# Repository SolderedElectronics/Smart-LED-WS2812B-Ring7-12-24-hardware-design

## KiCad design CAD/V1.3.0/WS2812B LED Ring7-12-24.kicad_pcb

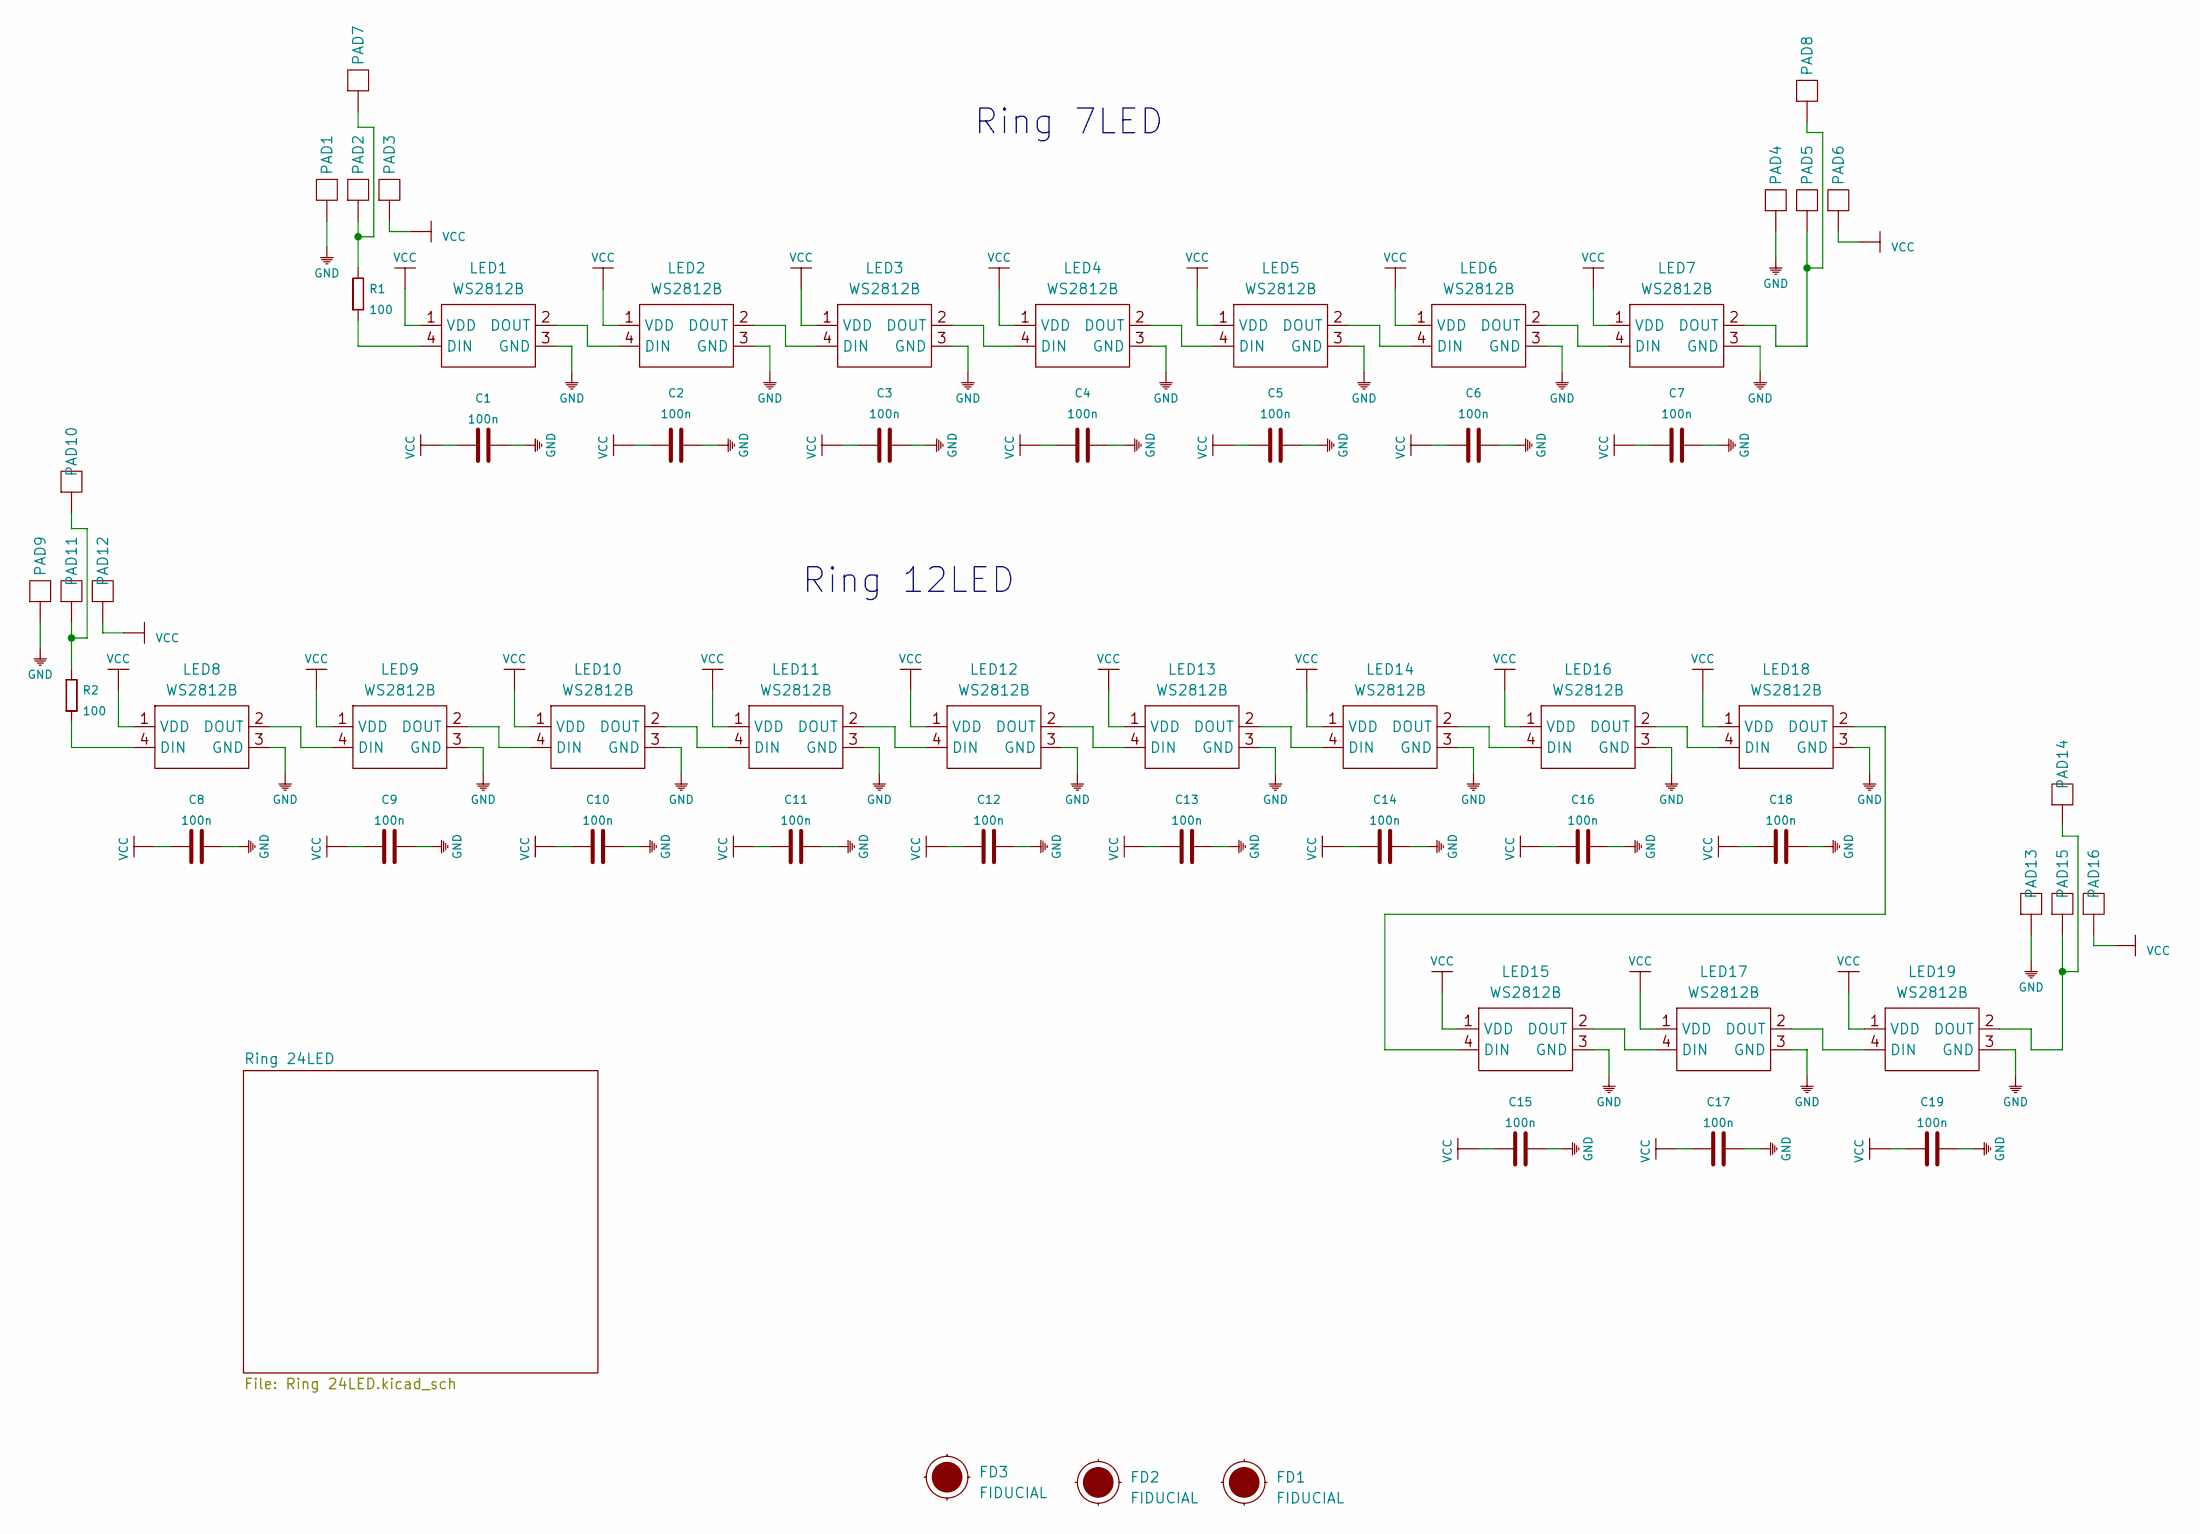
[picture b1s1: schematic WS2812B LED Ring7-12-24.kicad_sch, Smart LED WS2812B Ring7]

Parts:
C1, C2, C3, C4, C5, C6, C7, C8, C9, C10, C11, C12, C13, C14, C15, C16, C17, C18, C19: 100n; 0603C
FD1, FD2, FD3: FIDUCIAL; FIDUCIAL_23
LED1, LED2, LED3, LED4, LED5, LED6, LED7, LED8, LED9, LED10, LED11, LED12, LED13, LED14, LED15, LED16, LED17, LED18, LED19: WS2812B; WS2812B LED
PAD1, PAD2, PAD3, PAD4, PAD5, PAD6, PAD7, PAD8, PAD9, PAD10, PAD11, PAD12, PAD13, PAD14, PAD15, PAD16: PAD_2x1.5
R1, R2: 100; 0603R

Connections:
GND: C1.2, C2.2, C3.2, C4.2, C5.2, C6.2, C7.2, C8.2, C9.2, C10.2, C11.2, C12.2, C13.2, C14.2, C15.2, C16.2, C17.2, C18.2, C19.2, LED1.3 (GND), LED2.3 (GND), LED3.3 (GND), LED4.3 (GND), LED5.3 (GND), LED6.3 (GND), LED7.3 (GND), LED8.3 (GND), LED9.3 (GND), LED10.3 (GND), LED11.3 (GND), LED12.3 (GND), LED13.3 (GND), LED14.3 (GND), LED15.3 (GND), LED16.3 (GND), LED17.3 (GND), LED18.3 (GND), LED19.3 (GND), PAD1.1, PAD4.1, PAD9.1, PAD13.1; also elsewhere on the board
unnamed: LED1.2 (DOUT), LED2.4 (DIN)
unnamed: LED1.4 (DIN), R1.1
unnamed: LED2.2 (DOUT), LED3.4 (DIN)
unnamed: LED3.2 (DOUT), LED4.4 (DIN)
unnamed: LED4.2 (DOUT), LED5.4 (DIN)
unnamed: LED5.2 (DOUT), LED6.4 (DIN)
unnamed: LED6.2 (DOUT), LED7.4 (DIN)
unnamed: LED7.2 (DOUT), PAD5.1, PAD8.1
unnamed: LED8.2 (DOUT), LED9.4 (DIN)
unnamed: LED8.4 (DIN), R2.1
unnamed: LED10.2 (DOUT), LED11.4 (DIN)
unnamed: LED9.2 (DOUT), LED10.4 (DIN)
unnamed: LED11.2 (DOUT), LED12.4 (DIN)
unnamed: LED12.2 (DOUT), LED13.4 (DIN)
unnamed: LED13.2 (DOUT), LED14.4 (DIN)
unnamed: LED14.2 (DOUT), LED16.4 (DIN)
unnamed: LED15.2 (DOUT), LED17.4 (DIN)
unnamed: LED15.4 (DIN), LED18.2 (DOUT)
unnamed: LED16.2 (DOUT), LED18.4 (DIN)
unnamed: LED17.2 (DOUT), LED19.4 (DIN)
unnamed: LED19.2 (DOUT), PAD14.1, PAD15.1
unnamed: PAD2.1, PAD7.1, R1.2
unnamed: PAD10.1, PAD11.1, R2.2
VCC: C1.1, C2.1, C3.1, C4.1, C5.1, C6.1, C7.1, C8.1, C9.1, C10.1, C11.1, C12.1, C13.1, C14.1, C15.1, C16.1, C17.1, C18.1, C19.1, LED1.1 (VDD), LED2.1 (VDD), LED3.1 (VDD), LED4.1 (VDD), LED5.1 (VDD), LED6.1 (VDD), LED7.1 (VDD), LED8.1 (VDD), LED9.1 (VDD), LED10.1 (VDD), LED11.1 (VDD), LED12.1 (VDD), LED13.1 (VDD), LED14.1 (VDD), LED15.1 (VDD), LED16.1 (VDD), LED17.1 (VDD), LED18.1 (VDD), LED19.1 (VDD), PAD3.1, PAD6.1, PAD12.1, PAD16.1; also elsewhere on the board

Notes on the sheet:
Ring 12LED
Ring 7LED

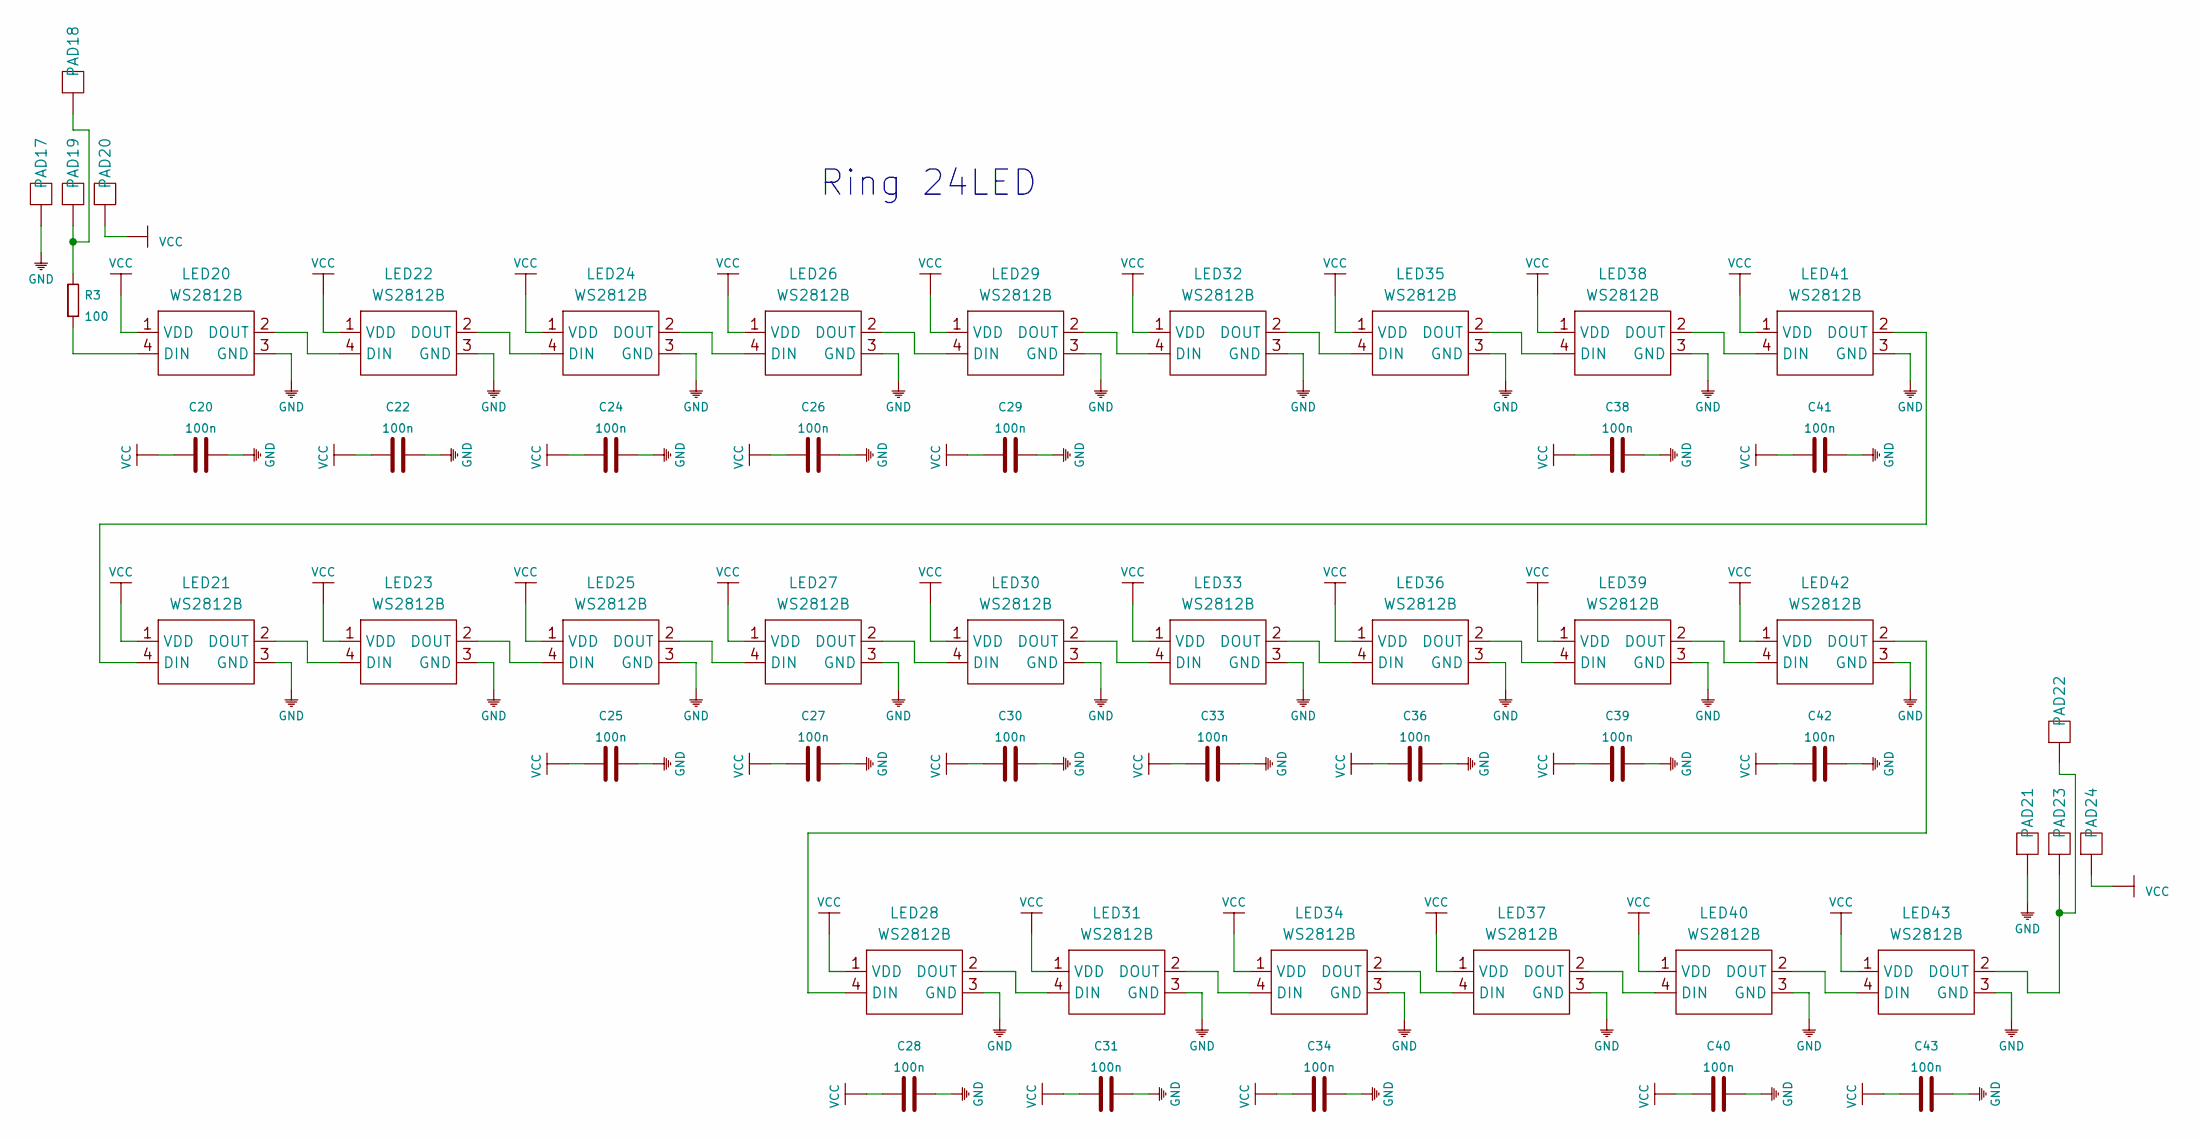
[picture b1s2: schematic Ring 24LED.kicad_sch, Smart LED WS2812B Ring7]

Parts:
C20, C22, C24, C25, C26, C27, C28, C29, C30, C31, C33, C34, C36, C38, C39, C40, C41, C42, C43: 100n; 0603C
LED20, LED21, LED22, LED23, LED24, LED25, LED26, LED27, LED28, LED29, LED30, LED31, LED32, LED33, LED34, LED35, LED36, LED37, LED38, LED39, LED40, LED41, LED42, LED43: WS2812B; WS2812B LED
PAD17, PAD18, PAD19, PAD20, PAD21, PAD22, PAD23, PAD24: PAD_2x1.5
R3: 100; 0603R

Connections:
GND: C20.2, C22.2, C24.2, C25.2, C26.2, C27.2, C28.2, C29.2, C30.2, C31.2, C33.2, C34.2, C36.2, C38.2, C39.2, C40.2, C41.2, C42.2, C43.2, LED20.3 (GND), LED21.3 (GND), LED22.3 (GND), LED23.3 (GND), LED24.3 (GND), LED25.3 (GND), LED26.3 (GND), LED27.3 (GND), LED28.3 (GND), LED29.3 (GND), LED30.3 (GND), LED31.3 (GND), LED32.3 (GND), LED33.3 (GND), LED34.3 (GND), LED35.3 (GND), LED36.3 (GND), LED37.3 (GND), LED38.3 (GND), LED39.3 (GND), LED40.3 (GND), LED41.3 (GND), LED42.3 (GND), LED43.3 (GND), PAD17.1, PAD21.1; also elsewhere on the board
unnamed: LED20.2 (DOUT), LED22.4 (DIN)
unnamed: LED20.4 (DIN), R3.1
unnamed: LED21.2 (DOUT), LED23.4 (DIN)
unnamed: LED21.4 (DIN), LED41.2 (DOUT)
unnamed: LED22.2 (DOUT), LED24.4 (DIN)
unnamed: LED23.2 (DOUT), LED25.4 (DIN)
unnamed: LED24.2 (DOUT), LED26.4 (DIN)
unnamed: LED25.2 (DOUT), LED27.4 (DIN)
unnamed: LED26.2 (DOUT), LED29.4 (DIN)
unnamed: LED27.2 (DOUT), LED30.4 (DIN)
unnamed: LED28.2 (DOUT), LED31.4 (DIN)
unnamed: LED28.4 (DIN), LED42.2 (DOUT)
unnamed: LED29.2 (DOUT), LED32.4 (DIN)
unnamed: LED30.2 (DOUT), LED33.4 (DIN)
unnamed: LED31.2 (DOUT), LED34.4 (DIN)
unnamed: LED32.2 (DOUT), LED35.4 (DIN)
unnamed: LED33.2 (DOUT), LED36.4 (DIN)
unnamed: LED34.2 (DOUT), LED37.4 (DIN)
unnamed: LED35.2 (DOUT), LED38.4 (DIN)
unnamed: LED36.2 (DOUT), LED39.4 (DIN)
unnamed: LED37.2 (DOUT), LED40.4 (DIN)
unnamed: LED38.2 (DOUT), LED41.4 (DIN)
unnamed: LED39.2 (DOUT), LED42.4 (DIN)
unnamed: LED40.2 (DOUT), LED43.4 (DIN)
unnamed: LED43.2 (DOUT), PAD22.1, PAD23.1
unnamed: PAD18.1, PAD19.1, R3.2
VCC: C20.1, C22.1, C24.1, C25.1, C26.1, C27.1, C28.1, C29.1, C30.1, C31.1, C33.1, C34.1, C36.1, C38.1, C39.1, C40.1, C41.1, C42.1, C43.1, LED20.1 (VDD), LED21.1 (VDD), LED22.1 (VDD), LED23.1 (VDD), LED24.1 (VDD), LED25.1 (VDD), LED26.1 (VDD), LED27.1 (VDD), LED28.1 (VDD), LED29.1 (VDD), LED30.1 (VDD), LED31.1 (VDD), LED32.1 (VDD), LED33.1 (VDD), LED34.1 (VDD), LED35.1 (VDD), LED36.1 (VDD), LED37.1 (VDD), LED38.1 (VDD), LED39.1 (VDD), LED40.1 (VDD), LED41.1 (VDD), LED42.1 (VDD), LED43.1 (VDD), PAD20.1, PAD24.1; also elsewhere on the board

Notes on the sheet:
Ring 24LED

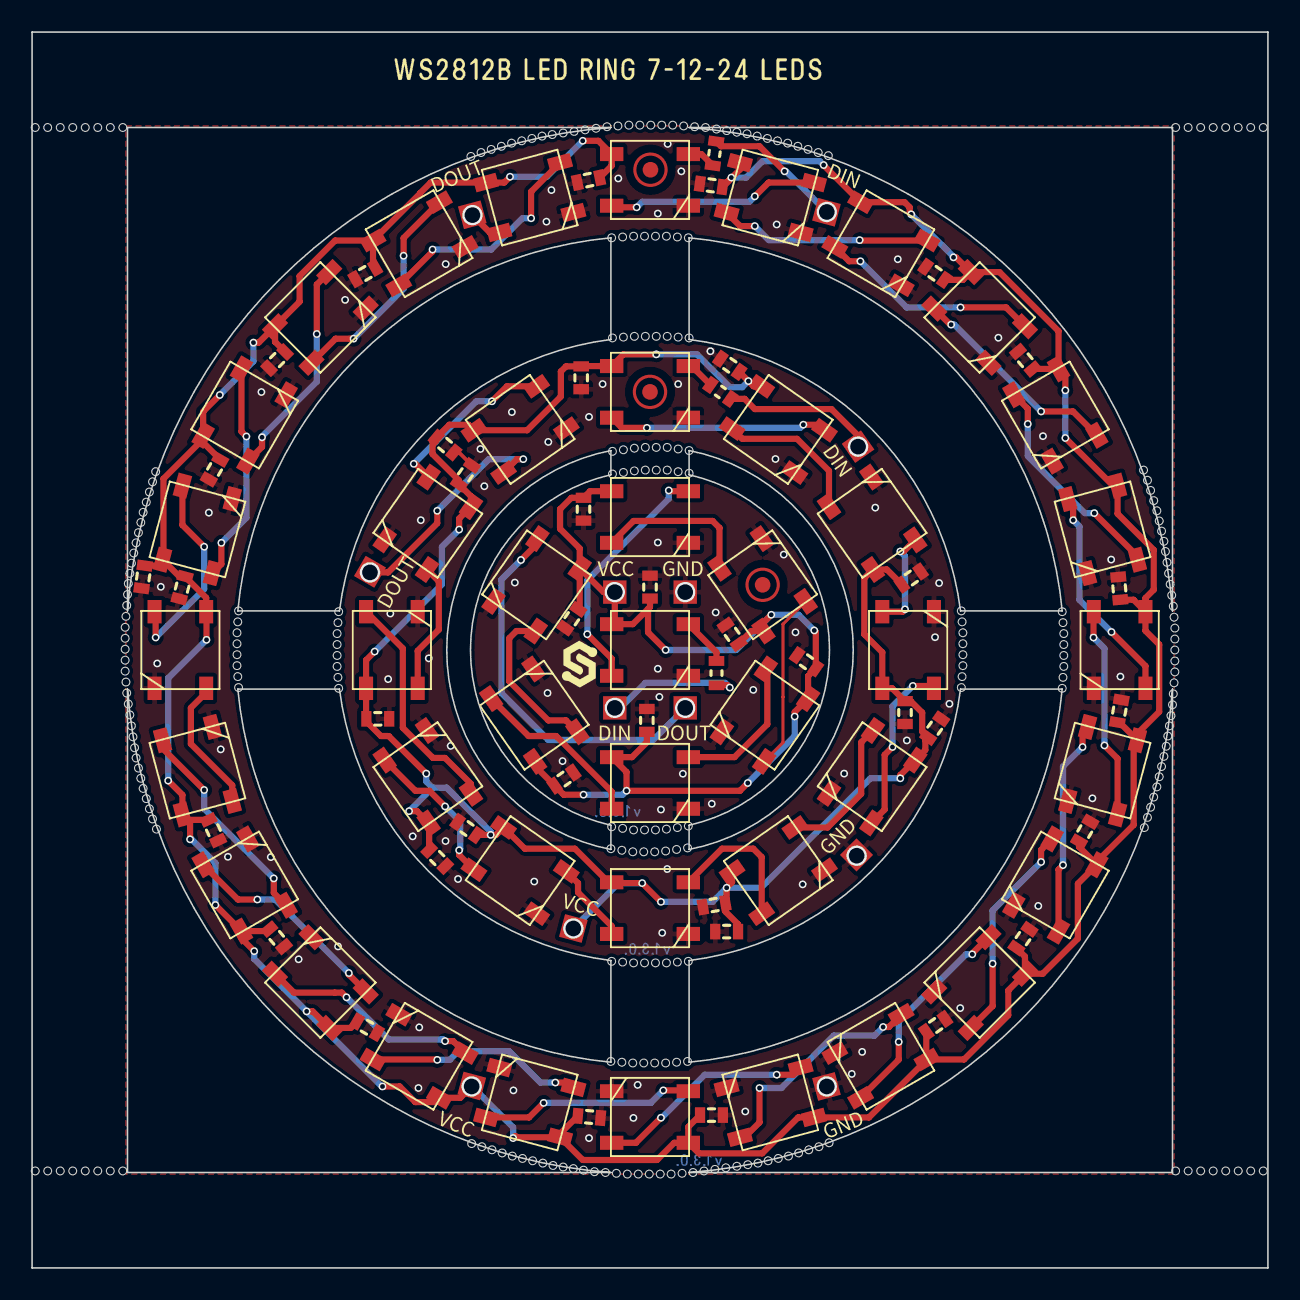
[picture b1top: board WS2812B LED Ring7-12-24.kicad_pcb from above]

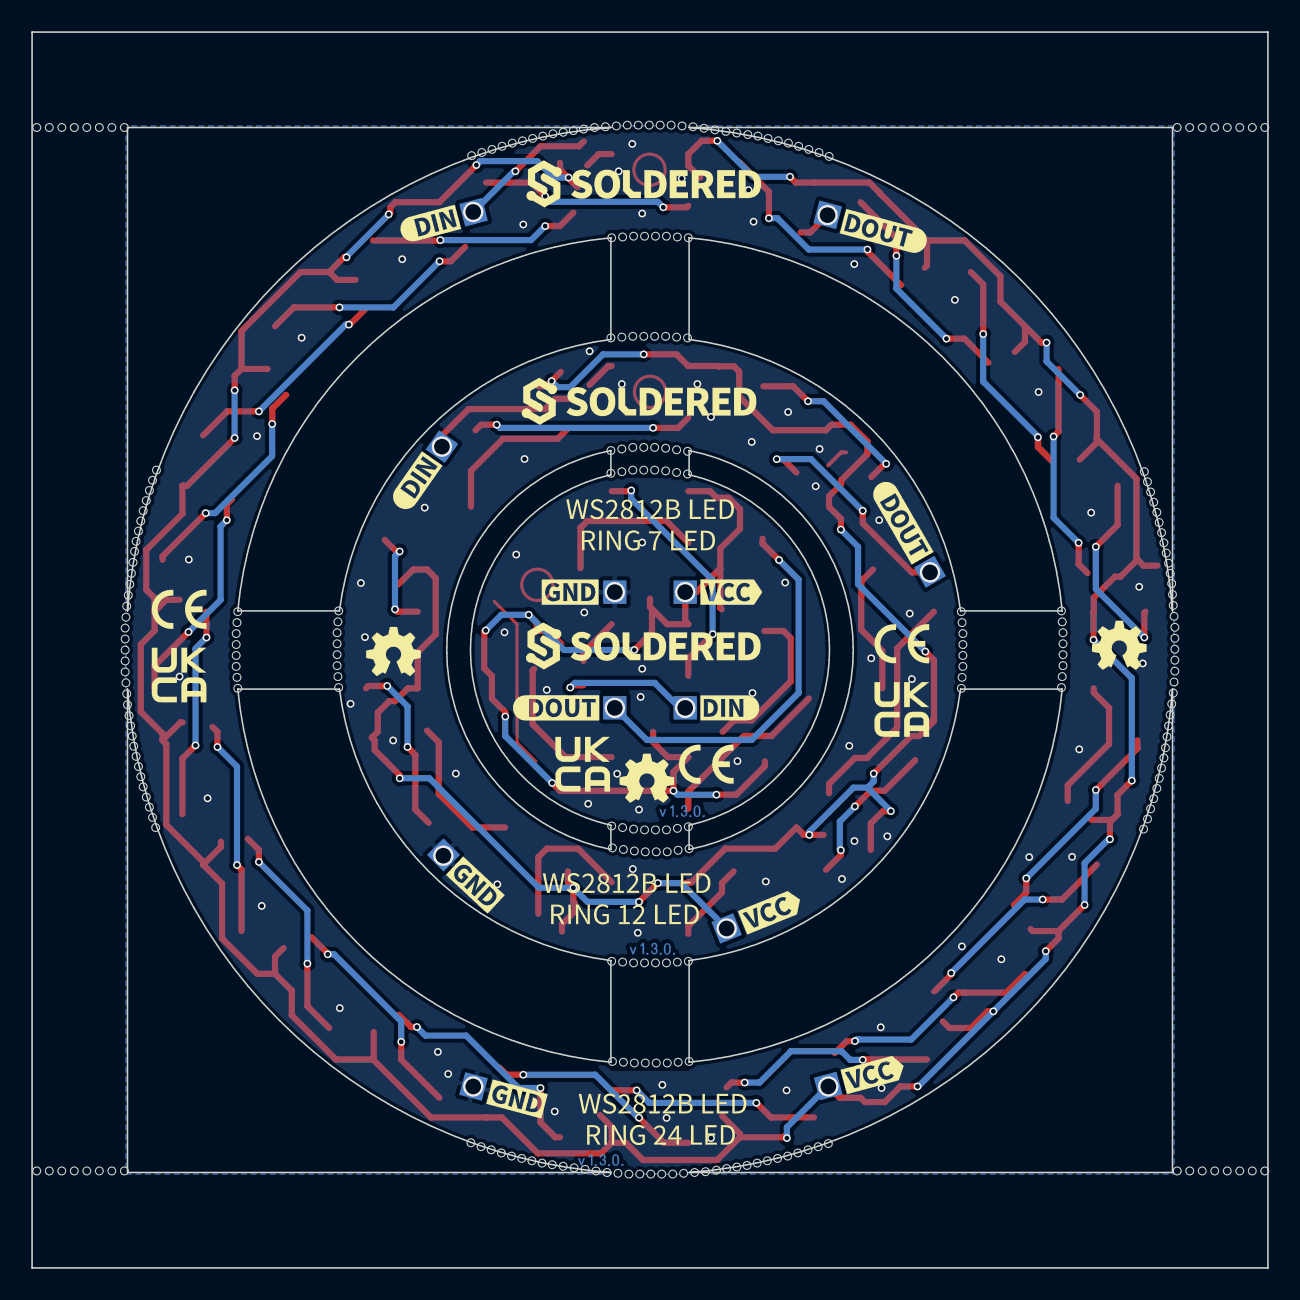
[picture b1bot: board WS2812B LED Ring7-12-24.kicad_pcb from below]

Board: 2 copper layers, 79.0 x 79.0 mm, 141 parts (25 on the bottom side), 51 nets.

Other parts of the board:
kibuzzard-65157A02: G***; kibuzzard-65157A02
kibuzzard-65157A32, kibuzzard-65157A32#2: G***; kibuzzard-65157A32
kibuzzard-651575D0, kibuzzard-651575D0#2, kibuzzard-651575D0#3: G***; kibuzzard-651575D0
kibuzzard-651575E0, kibuzzard-651575E0#2, kibuzzard-651575E0#3: G***; kibuzzard-651575E0
kibuzzard-651575F3, kibuzzard-651575F3#2, kibuzzard-651575F3#3: G***; kibuzzard-651575F3
kibuzzard-651575FD, kibuzzard-651575FD#2, kibuzzard-651575FD#3: G***; kibuzzard-651575FD
kibuzzard-651576A4: G***; kibuzzard-651576A4
kibuzzard-651576B4: G***; kibuzzard-651576B4
kibuzzard-6515768A: G***; kibuzzard-6515768A
kibuzzard-65157673, kibuzzard-65157673#2, kibuzzard-65157673#3: G***; kibuzzard-65157673
kibuzzard-65157800, kibuzzard-65157800#2, kibuzzard-65157800#3: G***; kibuzzard-65157800
kibuzzard-65157813, kibuzzard-65157813#2, kibuzzard-65157813#3: G***; kibuzzard-65157813
kibuzzard-65157826: G***; kibuzzard-65157826
kibuzzard-65157840, kibuzzard-65157840#2: G***; kibuzzard-65157840

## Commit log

2022-08-06 Updating open source files.
